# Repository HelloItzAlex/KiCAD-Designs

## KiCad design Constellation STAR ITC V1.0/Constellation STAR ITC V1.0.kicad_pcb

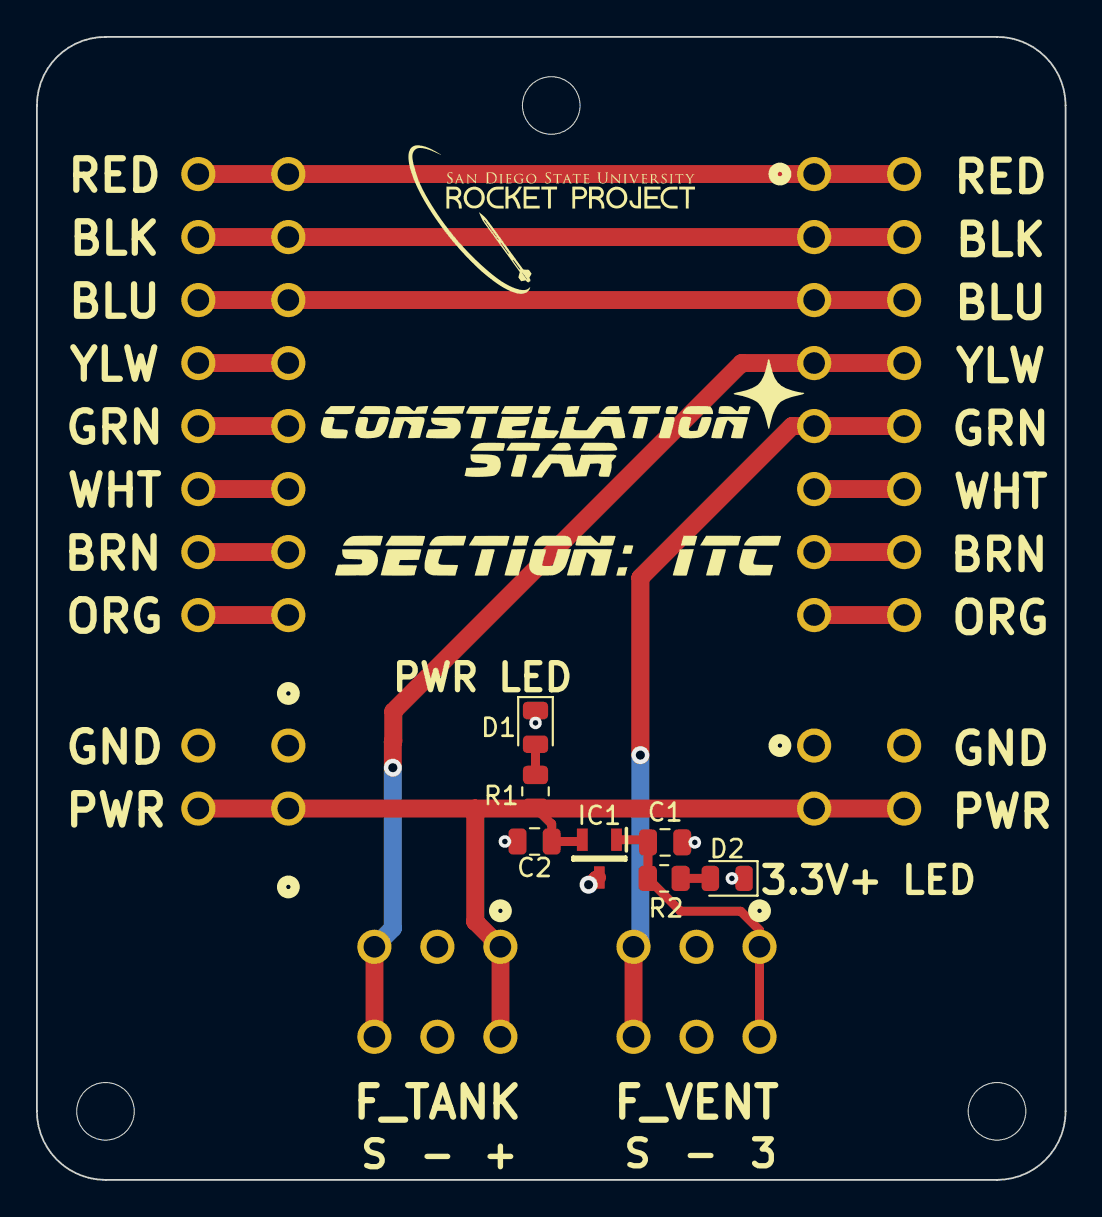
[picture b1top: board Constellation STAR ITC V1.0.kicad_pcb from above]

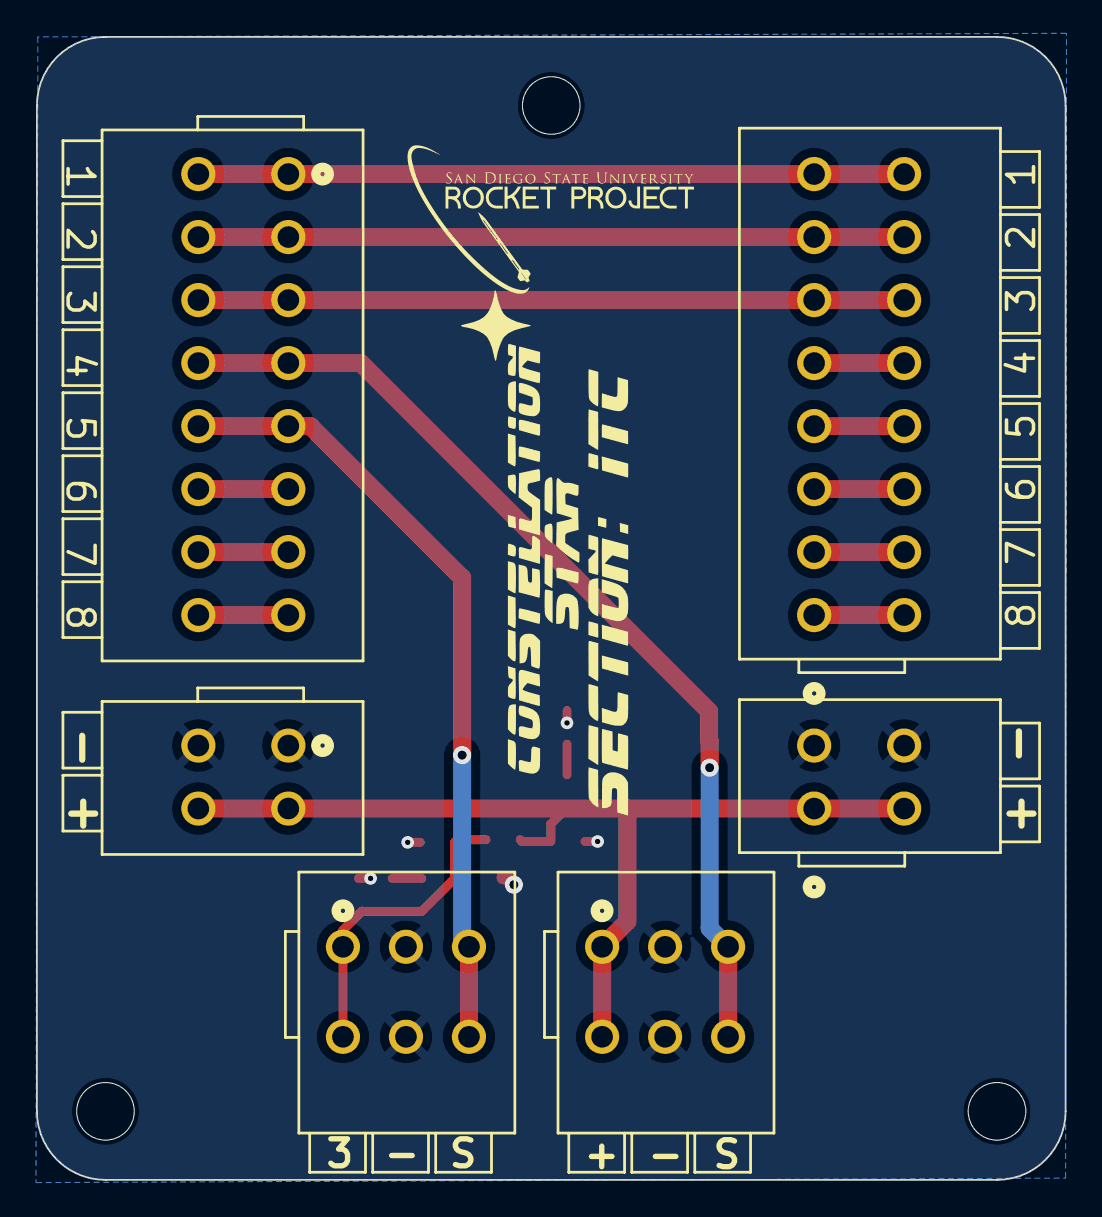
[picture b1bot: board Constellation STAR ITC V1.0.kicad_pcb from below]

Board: 2 copper layers, 57.1 x 63.5 mm, 16 parts (6 on the bottom side), 10 nets.

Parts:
C1, C2: 0.1uF; C_0805_2012Metric
D1, D2: RED; LED_0805_2012Metric
H1, H2, H3: MountingHole; MountingHole_3.2mm_M3
IC1: TLV76033DBZR; SOT95P237X112-3N
J1, J2: SIGNAL_OUT; CONN8_2601-1108_WAG
J3, J4: PWR IN; CONN2_2601-1102_WAG
J5: HALL_1; CONN3_2601-1103_WAG
J6: PT_1; CONN3_2601-1103_WAG
R1, R2: R; R_0805_2012Metric

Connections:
+3.3V: C1.1, IC1.1 (OUT), J5.1 (1_1), J5.2 (1_2), R2.1
ENG_CHAMBER: J1.15 (8_1), J1.16 (8_2), J2.1 (1_1), J2.2 (1_2)
F_TANK: J2.7 (4_1), J2.8 (4_2), J6.5 (3_1), J6.6 (3_2)
F_VENT: J2.9 (5_1), J2.10 (5_2), J5.5 (3_1), J5.6 (3_2)
GND: C1.2, C2.2, D1.1 (K), D2.1 (K), IC1.3 (GND), J3.3 (2_1), J3.4 (2_2), J4.1 (1_1), J4.2 (1_2), J5.3 (2_1), J5.4 (2_2), J6.3 (2_1), J6.4 (2_2)
MFV: J1.11 (6_1), J1.12 (6_2), J2.5 (3_1), J2.6 (3_2)
MOV: J1.13 (7_1), J1.14 (7_2), J2.3 (2_1), J2.4 (2_2)
unnamed: D1.2 (A), R1.2
unnamed: D2.2 (A), R2.2
VBUS: C2.1, IC1.2 (IN), J3.1 (1_1), J3.2 (1_2), J4.3 (2_1), J4.4 (2_2), J6.1 (1_1), J6.2 (1_2), R1.1

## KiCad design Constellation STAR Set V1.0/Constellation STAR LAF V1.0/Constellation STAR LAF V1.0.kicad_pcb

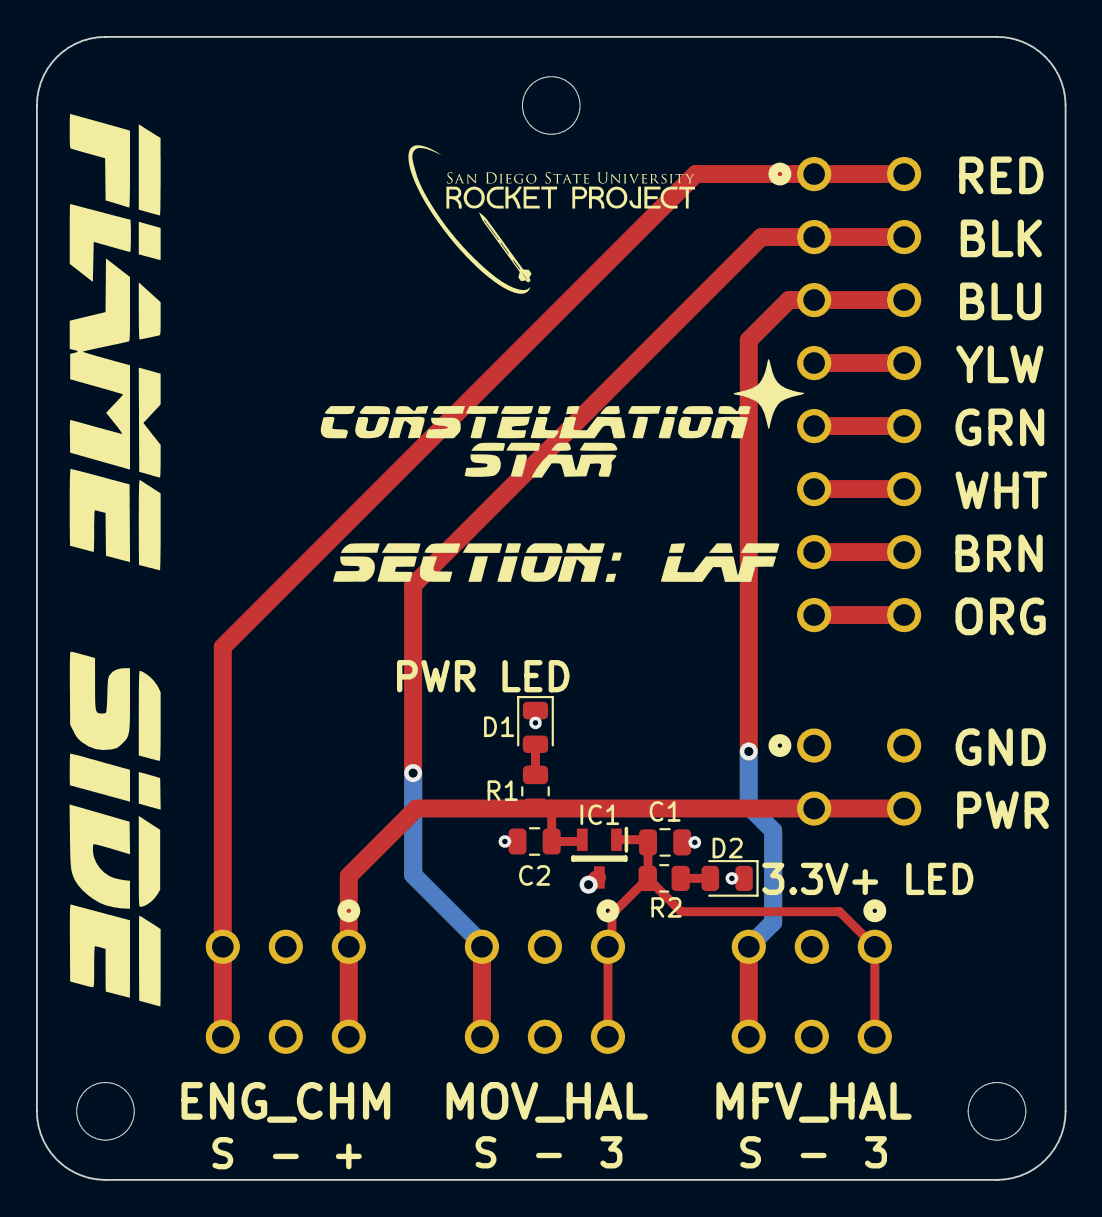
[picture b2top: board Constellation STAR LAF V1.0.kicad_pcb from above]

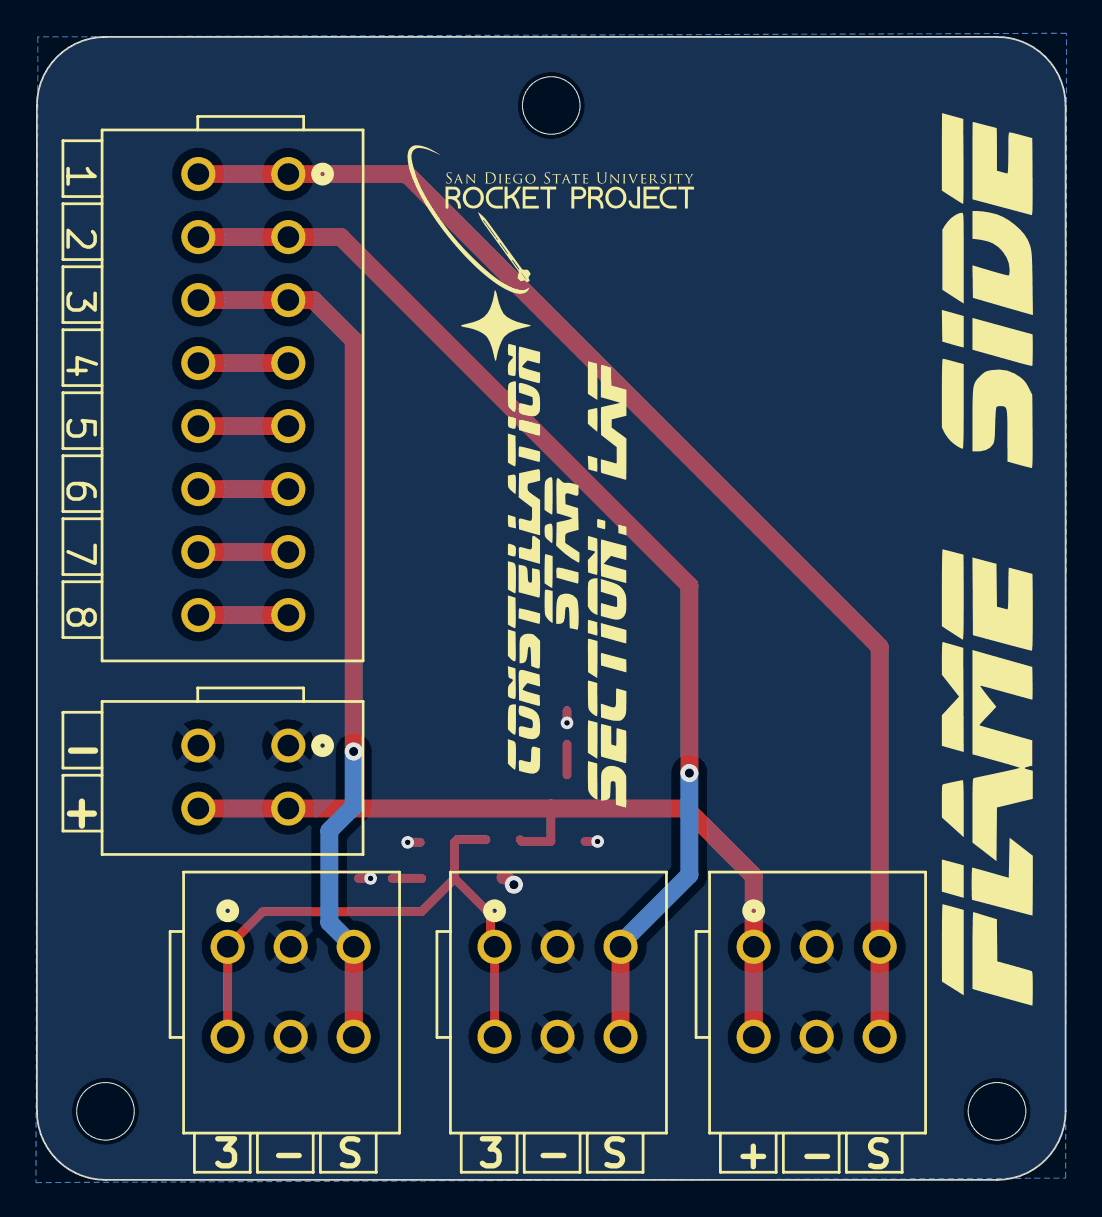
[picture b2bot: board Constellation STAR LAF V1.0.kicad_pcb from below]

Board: 2 copper layers, 57.1 x 63.5 mm, 15 parts (5 on the bottom side), 8 nets.

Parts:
C1, C2: 0.1uF; C_0805_2012Metric
D1: GREEN; LED_0805_2012Metric
D2: RED; LED_0805_2012Metric
H1, H2, H3: MountingHole; MountingHole_3.2mm_M3
IC1: TLV76033DBZR; SOT95P237X112-3N
J1: SIGNAL_OUT; CONN8_2601-1108_WAG
J2: PWR IN; CONN2_2601-1102_WAG
J3: HALL_1; CONN3_2601-1103_WAG
J4: HALL_2; CONN3_2601-1103_WAG
J5: PT_1; CONN3_2601-1103_WAG
R1: 470; R_0805_2012Metric
R2: 75; R_0805_2012Metric

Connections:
+3.3V: C1.1, IC1.1 (OUT), J3.1 (1_1), J3.2 (1_2), J4.1 (1_1), J4.2 (1_2), R2.1
ENG_CHAMBER: J1.1 (1_1), J1.2 (1_2), J5.5 (3_1), J5.6 (3_2)
GND: C1.2, C2.2, D1.1 (K), D2.1 (K), IC1.3 (GND), J2.1 (1_1), J2.2 (1_2), J3.3 (2_1), J3.4 (2_2), J4.3 (2_1), J4.4 (2_2), J5.3 (2_1), J5.4 (2_2)
MFV: J1.5 (3_1), J1.6 (3_2), J4.5 (3_1), J4.6 (3_2)
MOV: J1.3 (2_1), J1.4 (2_2), J3.5 (3_1), J3.6 (3_2)
unnamed: D1.2 (A), R1.2
unnamed: D2.2 (A), R2.2
VBUS: C2.1, IC1.2 (IN), J2.3 (2_1), J2.4 (2_2), J5.1 (1_1), J5.2 (1_2), R1.1

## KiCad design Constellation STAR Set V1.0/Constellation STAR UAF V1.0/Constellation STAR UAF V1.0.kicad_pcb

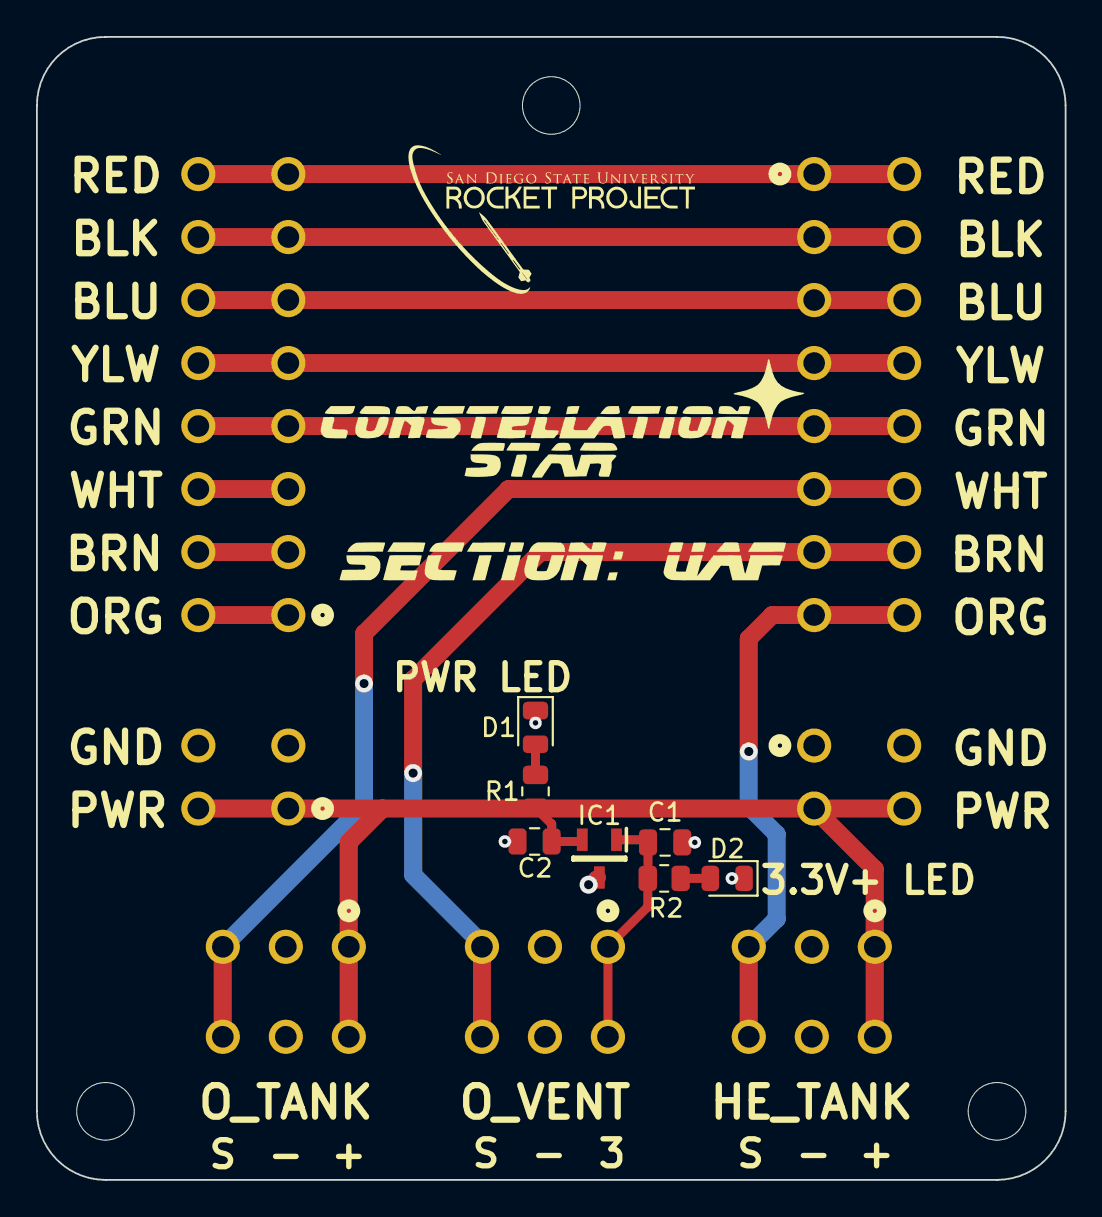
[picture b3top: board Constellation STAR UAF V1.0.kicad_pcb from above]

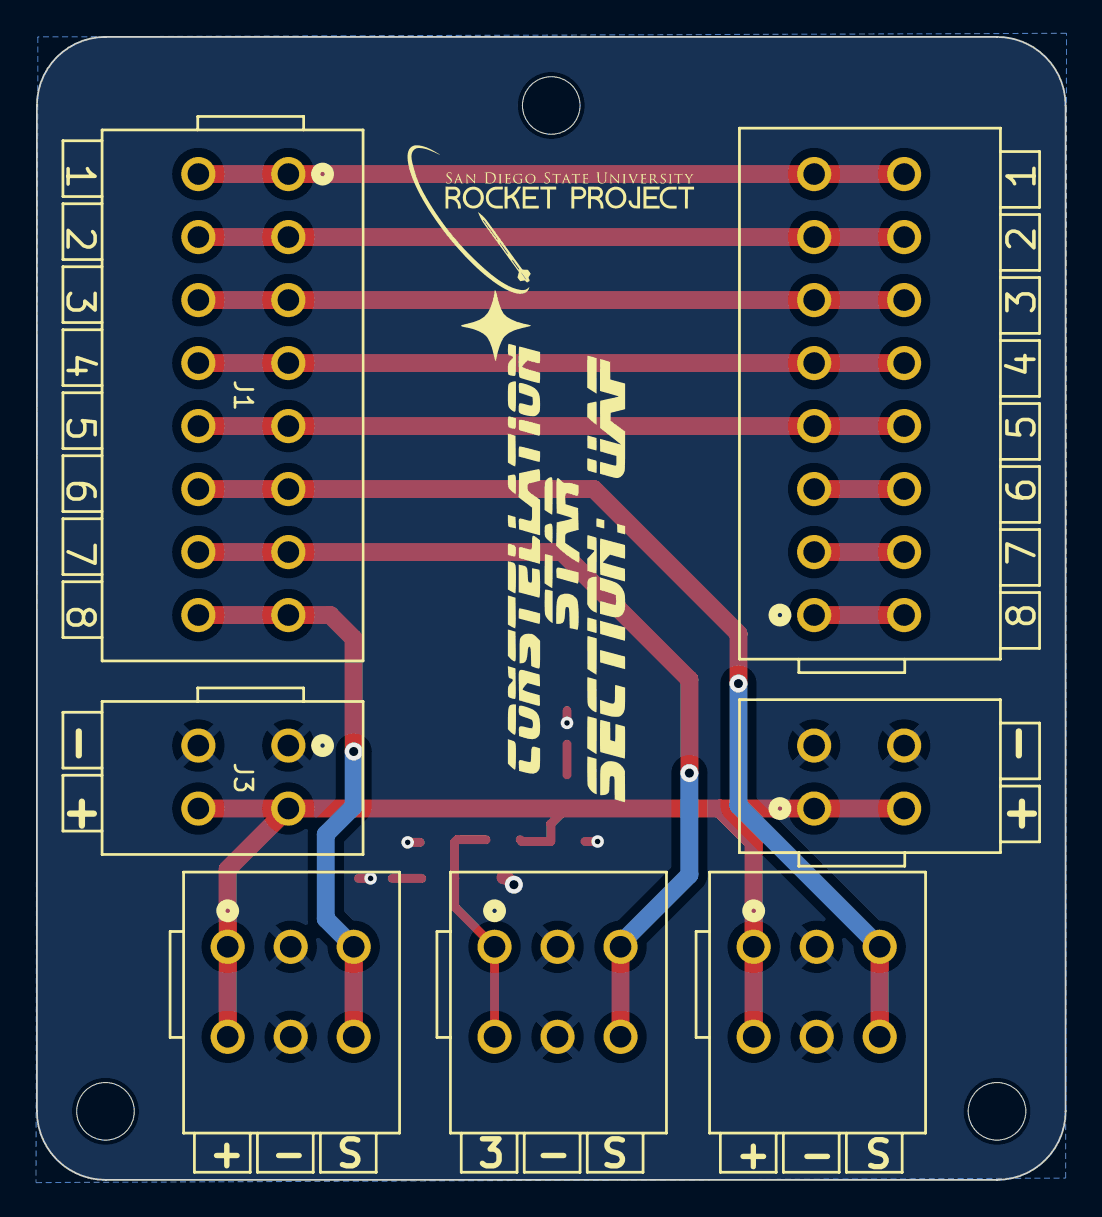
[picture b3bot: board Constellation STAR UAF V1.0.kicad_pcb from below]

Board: 2 copper layers, 57.1 x 63.5 mm, 17 parts (7 on the bottom side), 13 nets.

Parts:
C1, C2: 0.1uF; C_0805_2012Metric
D1: GREEN; LED_0805_2012Metric
D2: RED; LED_0805_2012Metric
H1, H2, H3: MountingHole; MountingHole_3.2mm_M3
IC1: TLV76033DBZR; SOT95P237X112-3N
J1, J2: SIGNAL_OUT; CONN8_2601-1108_WAG
J3, J4: PWR IN; CONN2_2601-1102_WAG
J5: HALL_1; CONN3_2601-1103_WAG
J6: PT_1; CONN3_2601-1103_WAG
J7: PT_2; CONN3_2601-1103_WAG
R1: 470; R_0805_2012Metric
R2: 75; R_0805_2012Metric

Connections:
+3.3V: C1.1, IC1.1 (OUT), J5.1 (1_1), J5.2 (1_2), R2.1
ENG_CHAMBER: J1.1 (1_1), J1.2 (1_2), J2.15 (8_1), J2.16 (8_2)
F_TANK: J1.7 (4_1), J1.8 (4_2), J2.9 (5_1), J2.10 (5_2)
F_VENT: J1.9 (5_1), J1.10 (5_2), J2.7 (4_1), J2.8 (4_2)
GND: C1.2, C2.2, D1.1 (K), D2.1 (K), IC1.3 (GND), J3.1 (1_1), J3.2 (1_2), J4.3 (2_1), J4.4 (2_2), J5.3 (2_1), J5.4 (2_2), J6.3 (2_1), J6.4 (2_2), J7.3 (2_1), J7.4 (2_2)
HE_TANK: J1.15 (8_1), J1.16 (8_2), J7.5 (3_1), J7.6 (3_2)
MFV: J1.5 (3_1), J1.6 (3_2), J2.11 (6_1), J2.12 (6_2)
MOV: J1.3 (2_1), J1.4 (2_2), J2.13 (7_1), J2.14 (7_2)
unnamed: D1.2 (A), R1.2
unnamed: D2.2 (A), R2.2
O_TANK: J1.11 (6_1), J1.12 (6_2), J6.5 (3_1), J6.6 (3_2)
O_VENT: J1.13 (7_1), J1.14 (7_2), J5.5 (3_1), J5.6 (3_2)
VBUS: C2.1, IC1.2 (IN), J3.3 (2_1), J3.4 (2_2), J4.1 (1_1), J4.2 (1_2), J6.1 (1_1), J6.2 (1_2), J7.1 (1_1), J7.2 (1_2), R1.1
